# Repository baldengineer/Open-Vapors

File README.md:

# Open Vapors - Open Source Reflow Oven Controller

Additional Information on [baldengineer.com]( https://www.baldengineer.com/?s=open+vapors).

Key hardware pieces you'll need:
+ Toaster Oven with "Always On"
+ Custom controller board (or maybe an Arduino)
+ SSR (Recommend Crydom D2425)
+ 4-Line RGB LCD Display
+ 5 Button Keypad
+ 1 Push Button
+ Piezo Buzzer 

## /code
Contains all of the code for the menu display and reflow controller.

## /KiCad
The revision 2 board is a significant redesign from the first board. It integrates the shift register for the LCD and implements voltage rails to massively reduce internal wiring. Headers were also position to logical places on the PCB.

Buzzer is optional, but now implemented. USB connection through a 0.1" (2.54mm) header to a USB-port breakout. It is only intended for serial operation.

Recommend using ISP for programming. 

Also added port for AT-09 BLE module. (Not yet implemented)

## /enclosure
Laser cut enclosure. The top, bottom, and sides used 3mm black acrylic. The front and back panels are Black on White acrylic.

Originally designed in Autocad Inventor, student edition. Then exported to Adobe Illustrator (CS6 I think) files.

The bottom needs to be redesigned to get more support. ~~The SSR warps it over time.~~ After almost 5 years, it hasn't sagged anymore. I would still recommend a support around the SSR though.

## /original electronics - EAGLE
Rev 1 was created using an EAGLE. It worked okay, but relied on a "LCD Backpack" and was not an optimized design. (LEDs in the wrong place.) 

That said, it worked great for years.

The original keypad is in use still. Even though the debounce caps were totally wrong.

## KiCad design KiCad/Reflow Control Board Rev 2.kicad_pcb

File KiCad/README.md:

## KiCad Files
The first design used EAGLE 6. I converted the EAGLE files into KiCad 5. This reduced the time to re-capture the schematic but it also caused a mess with the libraries and silk screens.

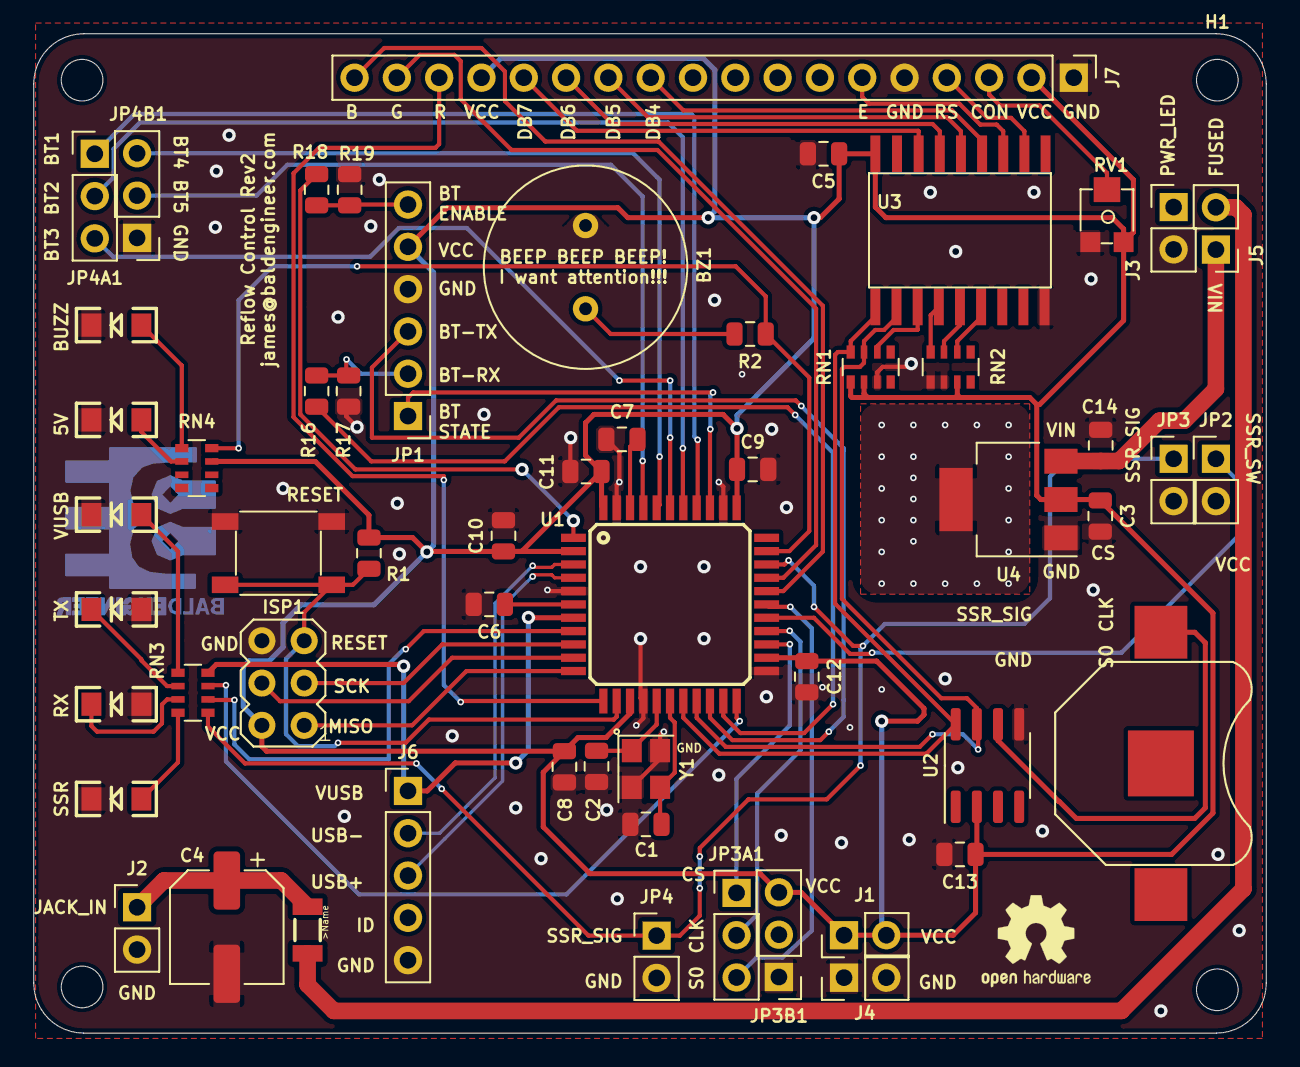
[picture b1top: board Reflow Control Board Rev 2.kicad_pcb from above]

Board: 2 copper layers, 74.0 x 60.0 mm, 62 parts (0 on the bottom side), 59 nets.

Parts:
BAT1: BATTERY12MM; BATTCON_12MM
BUZZ_IND1: LED1206; LED-1206
BZ1: Buzzer; 12mm_Piezo_Buzzer
C1, C2: 22p; C_0805_2012Metric
C3: 10u; C_0805_2012Metric
C4: 10u; CP_Elec_6.3x5.9
C5, C7, C8, C9, C10, C11, C12, C13: 100n; C_0805_2012Metric
C6, C14: 1u; C_0805_2012Metric
F1: PTCSMD; PTC-1206
H1, H2, H3, H4: MountingHole; MountingHole_2.5mm
ISP1: AVRISP-6; AVRISP
J1: VCC_Extra; PinHeader_1x02_P2.54mm_Vertical
J2: JACK; PinHeader_1x02_P2.54mm_Vertical
J3: SW_PWR_LED; PinHeader_1x02_P2.54mm_Vertical
J4: GND_Extra; PinHeader_1x02_P2.54mm_Vertical
J5: PWR_SW; PinHeader_1x02_P2.54mm_Vertical
J6: USB-Header; PinHeader_1x05_P2.54mm_Vertical
J7: LCD Header; PinHeader_1x18_P2.54mm_Vertical
JP1: BT Header; PinHeader_1x06_P2.54mm_Vertical
JP2: SSR Button; PinHeader_1x02_P2.54mm_Vertical
JP3: SSR LED; PinHeader_1x02_P2.54mm_Vertical
JP3A1: THERM; PinHeader_1x03_P2.54mm_Vertical
JP3B1: THERM-PWR; PinHeader_1x03_P2.54mm_Vertical
JP4: SSR CTRL; PinHeader_1x02_P2.54mm_Vertical
JP4A1: BTNa; PinHeader_1x03_P2.54mm_Vertical
JP4B1: BTNb; PinHeader_1x03_P2.54mm_Vertical
LOGO1: OSHW-LOGOM; OSHW-Logo2_7.3x6mm_SilkScreen
PWR_IND1: LED1206; LED-1206
R1: 10k; R_0805_2012Metric
R2: R; R_0805_2012Metric
R16, R17, R18, R19: R_Small; R_0805_2012Metric
RN1, RN2: 4K7; R_Array_Convex_4x0603
RN3, RN4: 1k; R_Array_Convex_4x0603
RV1: 10K; EVM3Y
RX_IND1: LED1206; LED-1206
S1: RESET; SW_Push_CK_PTS525_SM15
SSR_IND1: LED1206; LED-1206
TX_IND1: LED1206; LED-1206
U1: ATMEGA32U4-AU; TQFP44
U2: DS3231MZ; SOIC-8_3.9x4.9mm_P1.27mm
U3: MCP2300X_SO; SO18W
U4: NCP1117-5.0_SOT223; SOT-223-3_TabPin2
USB_PWR_IND1: LED1206; LED-1206
Y1: CRYSTALHC49US; Crystal_SMD_Abracon_ABM8G-4Pin_3.2x2.5mm
svg2mod: G***; BE20

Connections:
/BT1: JP4A1.1, U1.37
/BT2: JP4A1.2, U1.38
/BT3: JP4A1.3, U1.39
/BT4: JP4B1.3, U1.40
/BT5: JP4B1.2, U1.41
/BT-EN: R18.2, U1.1
/BT-ENABLE: JP1.6, R18.1, R19.1
/BT-RX: JP1.2, R16.1, R17.1
/BT-STATE: JP1.1, U1.36
/BT-TX: JP1.3, U1.20
/BUZZ_SIG: R2.1, RN4.2, U1.32
/CONTRAST: J7.3, RV1.2
/DB4: J7.11, U3.13
/DB5: J7.12, U3.14
/DB6: J7.13, U3.15
/DB7: J7.14, U3.16
/E: J7.6, U3.12
/FUSED: F1.2, J5.2
/I2C_SCL: RN1.2, U1.18, U2.8, U3.1
/I2C_SDA: RN1.4, U1.19, U2.7, U3.2
/JACK_IN: C4.1, F1.1, J2.1
/LCD_B: J7.18, U1.29
/LCD_G: J7.17, U1.30
/LCD_R: J7.16, U1.12
/MISO: ISP1.1, U1.11
/MOSI: ISP1.4, U1.10
/RESET: ISP1.5, R1.2, S1.1, U1.13
/RS: J7.4, U3.11
/RXLED: RN3.6, U1.8
/SCK: ISP1.3, U1.9
/SSR_SIG: JP3.1, JP4.1, RN3.8, U1.31
/SSR_SW: JP2.1, U1.27
/THERM_CLK: JP3A1.2, U1.26
/THERM_CS: JP3A1.1, U1.25
/THERM_S0: JP3A1.3, U1.28
/TXD: R16.2, U1.21
/TXLED: RN3.4, U1.22
/USB+: J6.3, U1.4
/USB-: J6.2, U1.3
/VIN: C14.1, J5.1, U4.3
/VUSB: J6.1, RN3.2, U1.7
GND: BUZZ_IND1.C, BZ1.2, C1.1, C2.1, C3.2, C4.2, C5.2, C6.2, C7.1, C8.2, C9.2, C10.2, C11.2, C12.2, C13.2, C14.2, ISP1.6, J2.2, J3.2, J4.1, J4.2, J6.5, J7.1, J7.5, JP1.4, JP2.2, JP3.2, JP3B1.1, JP4.2, JP4B1.1, PWR_IND1.C, R17.2, R19.2, RN1.5, RN2.1, RN2.3, RV1.1, RX_IND1.A, S1.2, SSR_IND1.C, TX_IND1.A, U1.5, U1.15, U1.23, U1.35, U1.43, U2.5, U3.9, U4.1, USB_PWR_IND1.C, Y1.2, Y1.4
unnamed: BAT1.PWR@2, U2.6
unnamed: BUZZ_IND1.A, RN4.1
unnamed: BZ1.1, R2.2
unnamed: C1.2, U1.17, Y1.3
unnamed: C2.2, U1.16, Y1.1
unnamed: C6.1, U1.6
unnamed: C7.2, U1.42
unnamed: PWR_IND1.A, RN4.3
unnamed: RN1.6, U3.3
unnamed: RN2.2, U3.4
unnamed: RN2.4, U3.5
unnamed: RN2.6, U3.6
unnamed: RN3.1, USB_PWR_IND1.A
unnamed: RN3.3, TX_IND1.C
unnamed: RN3.5, RX_IND1.C
unnamed: RN3.7, SSR_IND1.A
VCC: C3.1, C5.1, C8.1, C9.1, C10.1, C11.1, C12.1, C13.1, ISP1.2, J1.1, J1.2, J7.2, J7.15, JP1.5, JP3B1.3, R1.1, RN1.1, RN1.3, RN2.5, RN4.4, RV1.3, U1.2, U1.14, U1.24, U1.34, U1.44, U2.2, U3.18, U4.2

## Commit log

2017-04-26 adding readme
2021-09-15 overdue commit, prepping for v2 update
2021-09-15 added MIT license
2021-09-15 archiving original control board created in EAGLE
2021-09-15 rev board converted from EAGLE to KiCad
2021-09-15 big big v2 code update
2021-09-15 updated readme to reflect v2 notes
2021-09-25 initial BLE support reporting current temperature
2021-09-29 change the soak state to accomodate proper soaking. also changed thermal timeout to be absolute value to account for if the temperature drops.
2021-09-29 fixed soak stage bug, fix manual SSR control, added max temperature check
2022-02-08 adding image
2022-02-08 added 3d render image, because pretty
2022-02-08 Added PDF of the schematic.
